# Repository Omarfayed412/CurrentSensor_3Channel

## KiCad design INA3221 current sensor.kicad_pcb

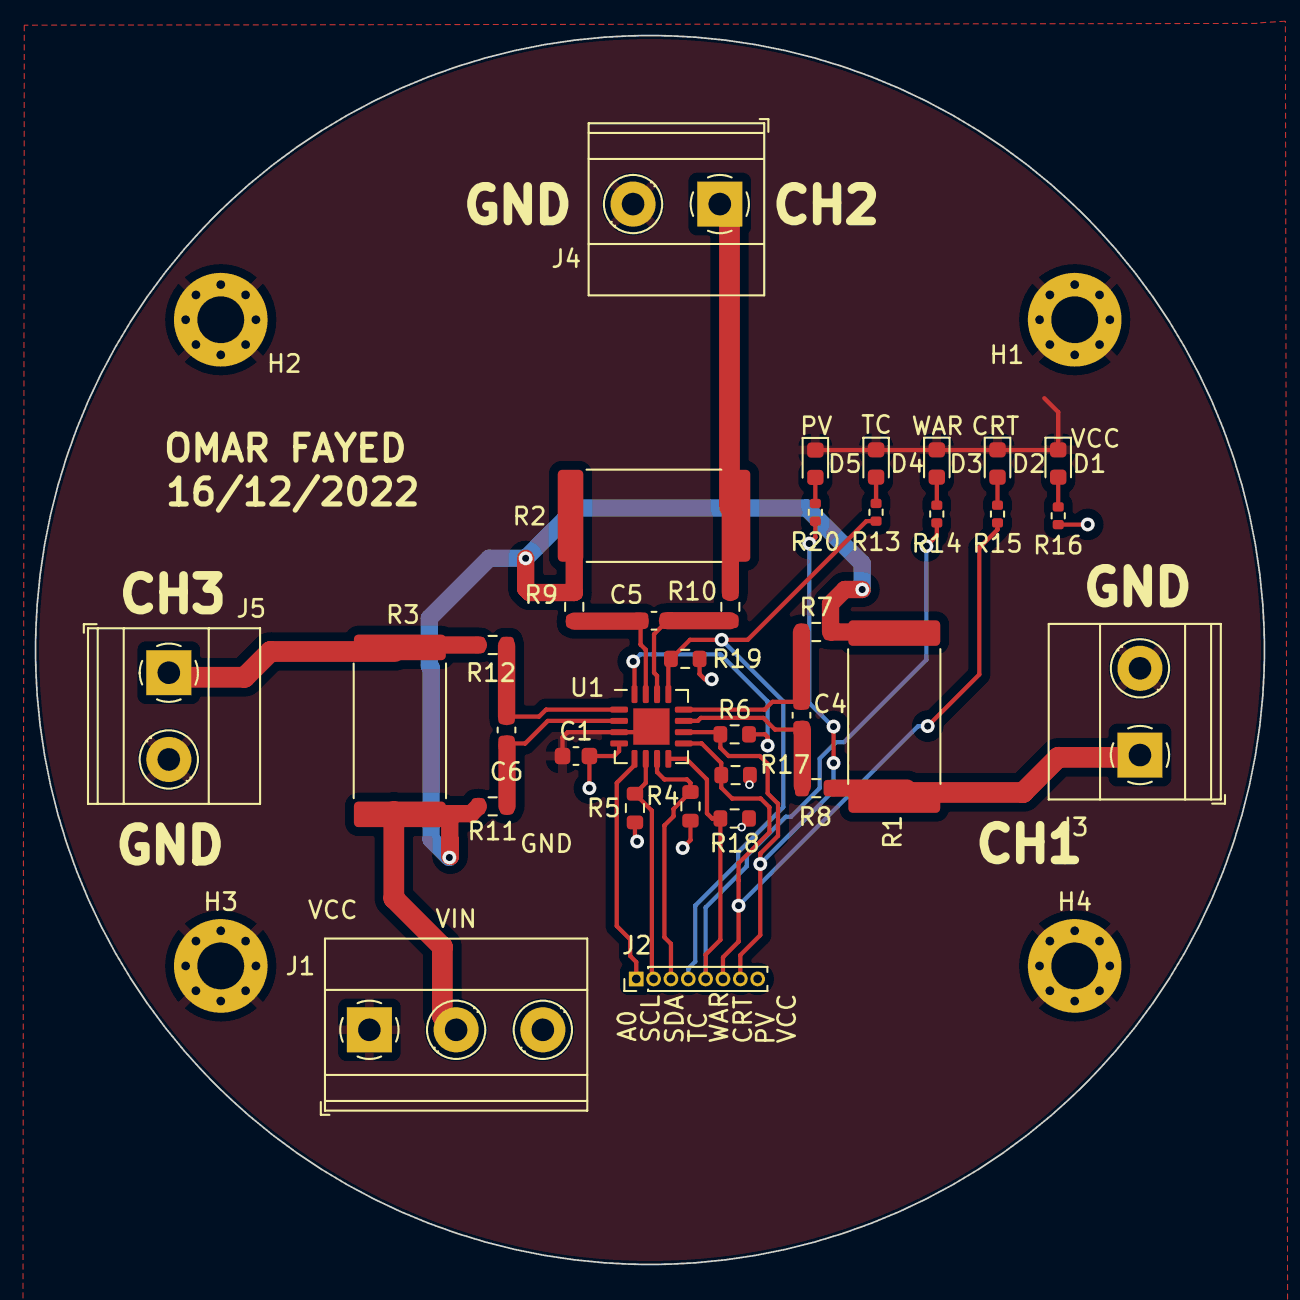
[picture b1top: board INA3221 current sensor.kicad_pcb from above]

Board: 2 copper layers, 70.8 x 70.8 mm, 39 parts (0 on the bottom side), 25 nets.

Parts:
C1, C4, C5, C6: 0.1uF; C_0603_1608Metric
D1, D2, D3, D4, D5: LED; LED_0603_1608Metric
H1, H2, H3, H4: MountingHole_Pad; MountingHole_2.7mm_M2.5_Pad_Via
J1: Screw_Terminal_01x03; TerminalBlock_Phoenix_MKDS-1,5-3_1x03_P5.00mm_Horizontal
J2: Conn_01x08_Female; PinHeader_1x08_P1.00mm_Vertical
J3, J4, J5: Screw_Terminal_01x02; TerminalBlock_Phoenix_MKDS-1,5-2_1x02_P5.00mm_Horizontal
R1, R2, R3: 1R; R_4020_10251Metric
R4, R5, R17, R18, R19: 10K; R_0603_1608Metric
R6: 10k; R_0603_1608Metric
R7, R8, R9, R10, R11, R12: 10R; R_0603_1608Metric
R13, R14, R15, R16, R20: 330R; R_0402_1005Metric
U1: INA3221; Texas_RGV_S-PVQFN-N16_EP2.1x2.1mm

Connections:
A0: J2.1, U1.5 (A0)
CRITICAL: J2.6, R15.1, R17.2, U1.9 (CRITICAL)
GND: C1.1, D1.1 (K), D2.1 (K), D3.1 (K), D4.1 (K), D5.1 (K), H1.1, H2.1, H3.1, H4.1, J1.1, J3.2, J4.2, J5.2, U1.3 (GND), U1.17 (EP)
IN+1: J1.2, R1.1, R2.1, R3.1, R7.2, R9.2, R11.2
IN-1: J3.1, R1.2, R8.2
IN-2: J4.1, R2.2, R10.2
IN-3: J5.1, R3.2, R12.2
unnamed: C4.1, R8.1, U1.11 (IN-1)
unnamed: C4.2, R7.1, U1.12 (IN+1)
unnamed: C5.1, R10.1, U1.14 (IN-2)
unnamed: C5.2, R9.1, U1.15 (IN+2)
unnamed: C6.1, R12.1, U1.1 (IN-3)
unnamed: C6.2, R11.1, U1.2 (IN+3)
unnamed: D1.2 (A), R16.2
unnamed: D2.2 (A), R15.2
unnamed: D3.2 (A), R14.2
unnamed: D4.2 (A), R13.2
unnamed: D5.2 (A), R20.2
unnamed: R6.2, U1.16 (VPU)
PV: J2.7, R6.1, R20.1, U1.10 (PV)
SCL: J2.2, R5.2, U1.6 (SCL)
SDA: J2.3, R4.2, U1.7 (SDA)
TC: J2.4, R13.1, R19.2, U1.13 (TC)
VCC: C1.2, J1.3, J2.8, R4.1, R5.1, R16.1, R17.1, R18.1, R19.1, U1.4 (VS)
WARN: J2.5, R14.1, R18.2, U1.8 (WARNING)

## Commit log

2023-11-23 Added all the design files for PCB in Kicad
